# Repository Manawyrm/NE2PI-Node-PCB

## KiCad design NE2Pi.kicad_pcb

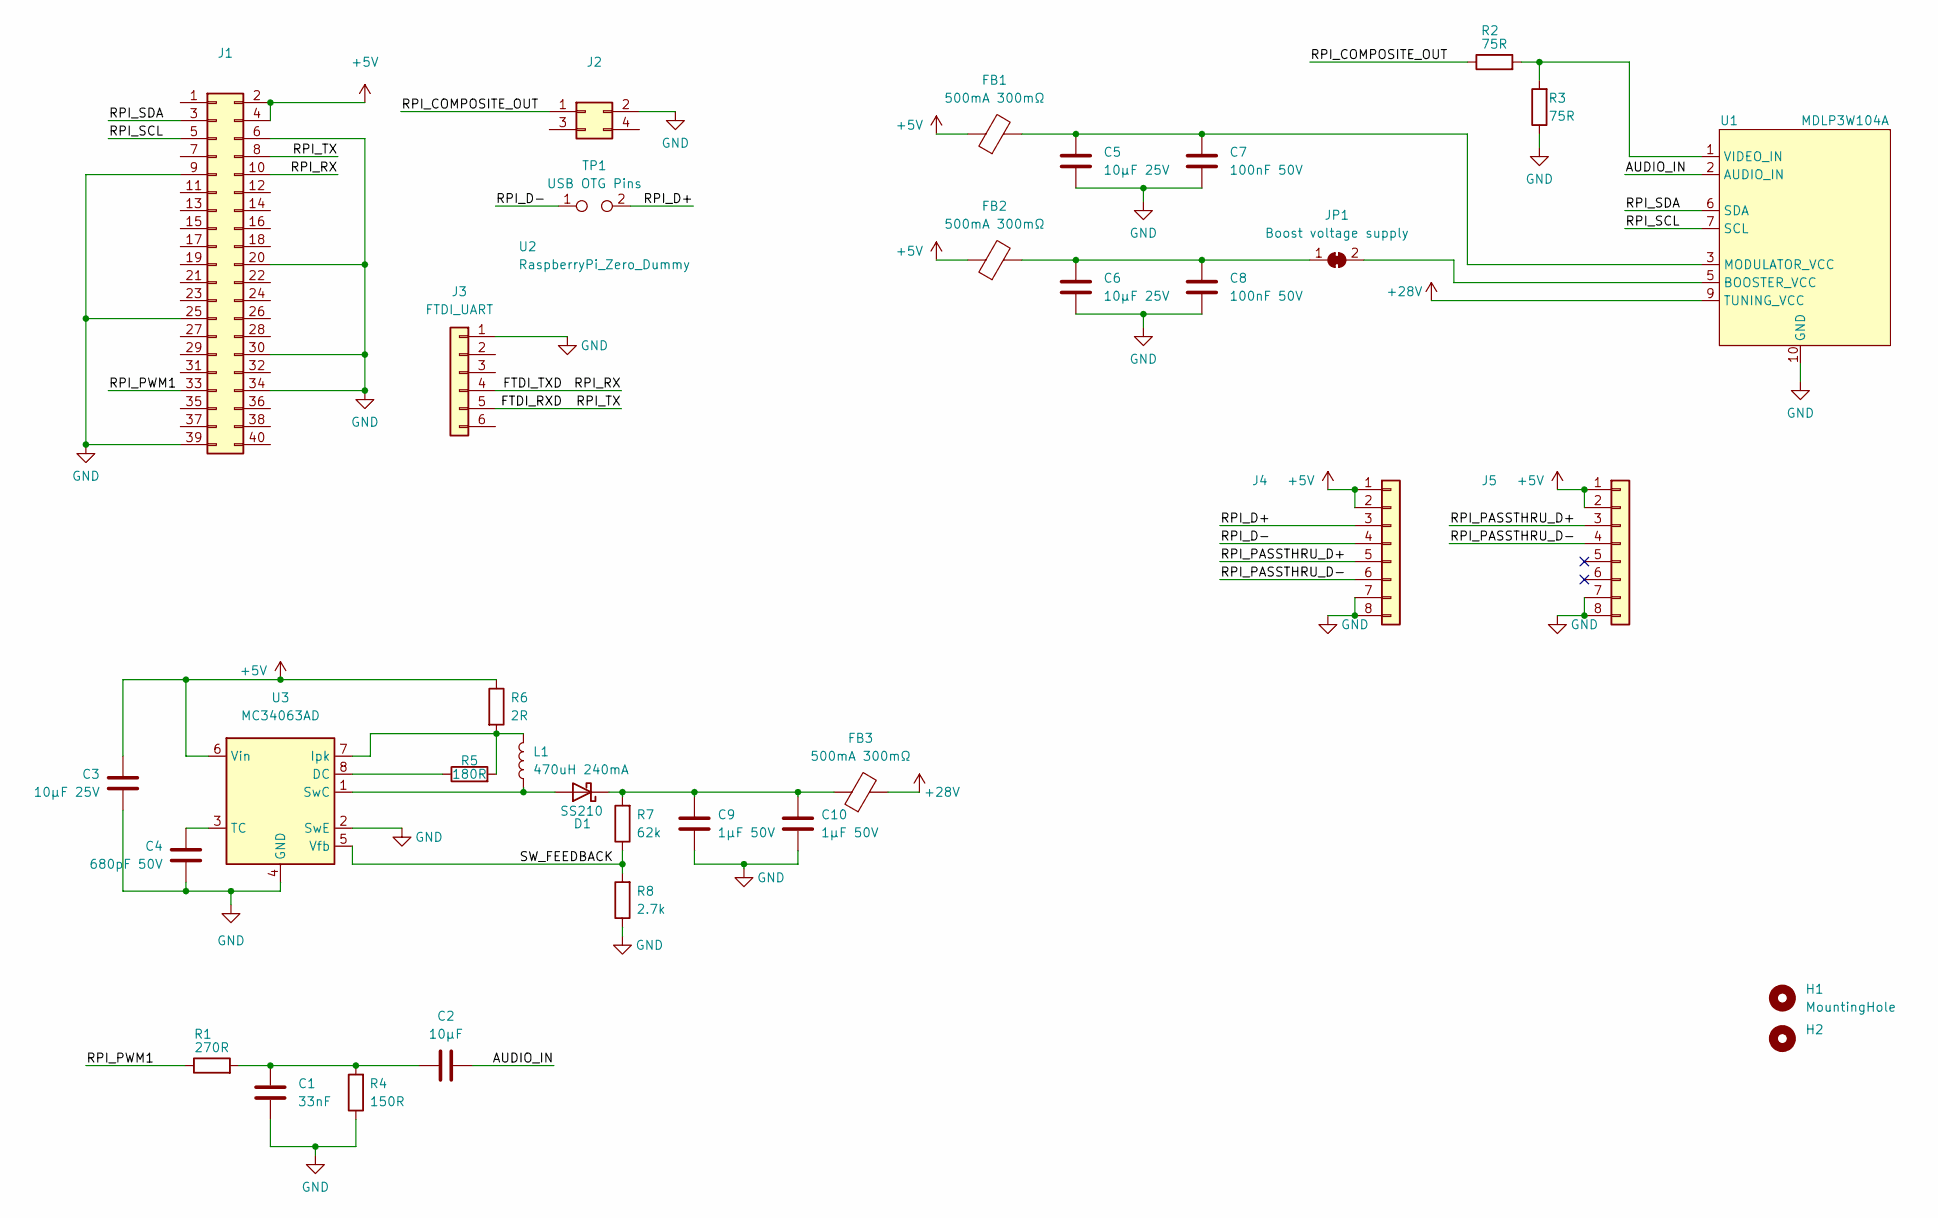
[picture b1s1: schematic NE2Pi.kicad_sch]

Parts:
C1: 33nF; C_0805_2012Metric_Pad1.18x1.45mm_HandSolder; LCSC C1739
C2: 10µF; C_0805_2012Metric_Pad1.18x1.45mm_HandSolder; LCSC C15850
C3, C5, C6: 10µF 25V; C_0805_2012Metric_Pad1.18x1.45mm_HandSolder; LCSC C15850
C4: 680pF 50V; R_0805_2012Metric; LCSC C53150
C7, C8: 100nF 50V; C_0805_2012Metric_Pad1.18x1.45mm_HandSolder; LCSC C49678
C9, C10: 1µF 50V; C_1206_3216Metric; LCSC C1848
D1: SS210; D_SMA; LCSC C14996
FB1, FB2, FB3: 500mA 300mΩ; L_0805_2012Metric_Pad1.05x1.20mm_HandSolder; LCSC C1017
H1: MountingHole; ToolingHole_JLCSMT
H2: (no value)
J1: LCSC C2977589
J2: LCSC C2977590
J3: FTDI_UART; PinHeader_1x06_P2.54mm_Vertical
J4: LCSC C2833721
J5: LCSC C2833322
JP1: Boost voltage supply; SolderJumper-2_P1.3mm_Bridged_Pad1.0x1.5mm
L1: 470uH 240mA; L_7.3x7.3_H3.5; LCSC C718275
R1: 270R; R_0805_2012Metric_Pad1.20x1.40mm_HandSolder; LCSC C17590
R2, R3: 75R; R_0805_2012Metric_Pad1.20x1.40mm_HandSolder; LCSC C20638
R4: 150R; R_0805_2012Metric_Pad1.20x1.40mm_HandSolder; LCSC C17471
R5: 180R; R_0805_2012Metric; LCSC C25270
R6: 2R; R_0805_2012Metric; LCSC C17606
R7: 62k; R_0805_2012Metric; LCSC C17783
R8: 2.7k; R_0805_2012Metric; LCSC C17530
TP1: USB OTG Pins; PinHeader_1x02_P2.54mm_Vertical
U1: MDLP3W104A; ALPS_MDLP3W104A
U2: RaspberryPi_Zero_Dummy; RaspberryPiZero_Dummy
U3: MC34063AD; SOIC-8_3.9x4.9mm_P1.27mm; LCSC C32078

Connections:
+5V: C3.2, FB1.1, FB2.1, J1.2, J1.4, J4.1, J4.2, J5.1, J5.2, R6.1, U3.6 (Vin)
+28V: FB3.2, U1.9 (TUNING_VCC)
/AUDIO_IN: C2.2, U1.2 (AUDIO_IN)
/FTDI_RXD: J1.8, J3.5
/FTDI_TXD: J1.10, J3.4
/RPI_COMPOSITE_OUT: J2.1, R2.1
/RPI_D+: J4.3, TP1.2
/RPI_D-: J4.4, TP1.1
/RPI_PASSTHRU_D+: J4.5, J5.3
/RPI_PASSTHRU_D-: J4.6, J5.4
/RPI_PWM1: J1.33, R1.1
/RPI_SCL: J1.5, U1.7 (SCL)
/RPI_SDA: J1.3, U1.6 (SDA)
/SW_FEEDBACK: R7.1, R8.2, U3.5 (Vfb)
GND: C1.2, C3.1, C4.1, C5.2, C6.2, C7.2, C8.2, C9.2, C10.2, J1.6, J1.9, J1.20, J1.25, J1.30, J1.34, J1.39, J2.2, J3.1, J4.7, J4.8, J5.7, J5.8, R3.1, R4.1, R8.1, U1.10 (GND), U3.2 (SwE), U3.4 (GND)
unnamed: C1.1, C2.1, R1.2, R4.2
unnamed: C4.2, U3.3 (TC)
unnamed: C5.1, C7.1, FB1.2, U1.3 (MODULATOR_VCC)
unnamed: C6.1, C8.1, FB2.2, JP1.1 (A)
unnamed: C9.1, C10.1, D1.1 (K), FB3.1, R7.2
unnamed: D1.2 (A), L1.1, U3.1 (SwC)
unnamed: JP1.2 (B), U1.5 (BOOSTER_VCC)
unnamed: L1.2, R5.2, R6.2, U3.7 (Ipk)
unnamed: R2.2, R3.2, U1.1 (VIDEO_IN)
unnamed: R5.1, U3.8 (DC)

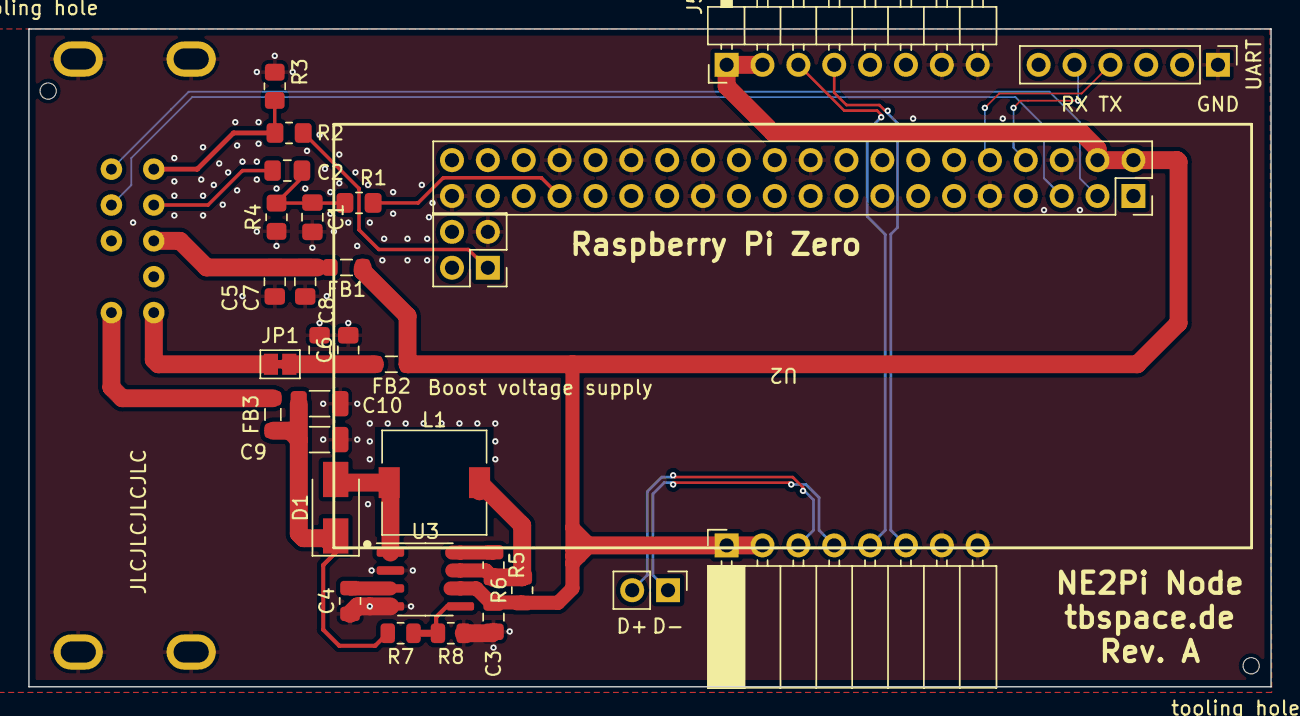
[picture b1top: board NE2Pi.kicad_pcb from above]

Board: 2 copper layers, 88.0 x 46.6 mm, 35 parts (0 on the bottom side), 25 nets.

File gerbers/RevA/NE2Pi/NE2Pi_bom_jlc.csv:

"Comment","Designator","Footprint","LCSC Part #"
"33nF","C1","C_0805_2012Metric_Pad1.18x1.45mm_HandSolder","C1739"
"10µF","C2","C_0805_2012Metric_Pad1.18x1.45mm_HandSolder","C15850"
"10µF 25V","C3,C5,C6","C_0805_2012Metric_Pad1.18x1.45mm_HandSolder","C15850"
"680pF 50V","C4","R_0805_2012Metric","C53150"
"100nF 50V","C7,C8","C_0805_2012Metric_Pad1.18x1.45mm_HandSolder","C49678"
"1µF 50V","C9,C10","C_1206_3216Metric","C1848"
"SS210","D1","D_SMA","C14996"
"500mA 300mΩ","FB1,FB2,FB3","L_0805_2012Metric_Pad1.05x1.20mm_HandSolder","C1017"
"Raspberry_Pi_Header","J1","PinSocket_2x20_P2.54mm_Vertical","C2977589"
"Raspberry_Pi_TV_Header","J2","PinSocket_2x02_P2.54mm_Vertical","C2977590"
"Backplane Bottom","J4","PinSocket_1x08_P2.54mm_Horizontal","C2833721"
"Backplane Passthru","J5","PinHeader_1x08_P2.54mm_Horizontal","C2833322"
"470uH 240mA","L1","L_7.3x7.3_H3.5","C718275"
"270R","R1","R_0805_2012Metric_Pad1.20x1.40mm_HandSolder","C17590"
"75R","R2,R3","R_0805_2012Metric_Pad1.20x1.40mm_HandSolder","C20638"
"150R","R4","R_0805_2012Metric_Pad1.20x1.40mm_HandSolder","C17471"
"180R","R5","R_0805_2012Metric","C25270"
"2R","R6","R_0805_2012Metric","C17606"
"62k","R7","R_0805_2012Metric","C17783"
"2.7k","R8","R_0805_2012Metric","C17530"
"MC34063AD","U3","SOIC-8_3.9x4.9mm_P1.27mm","C32078"
